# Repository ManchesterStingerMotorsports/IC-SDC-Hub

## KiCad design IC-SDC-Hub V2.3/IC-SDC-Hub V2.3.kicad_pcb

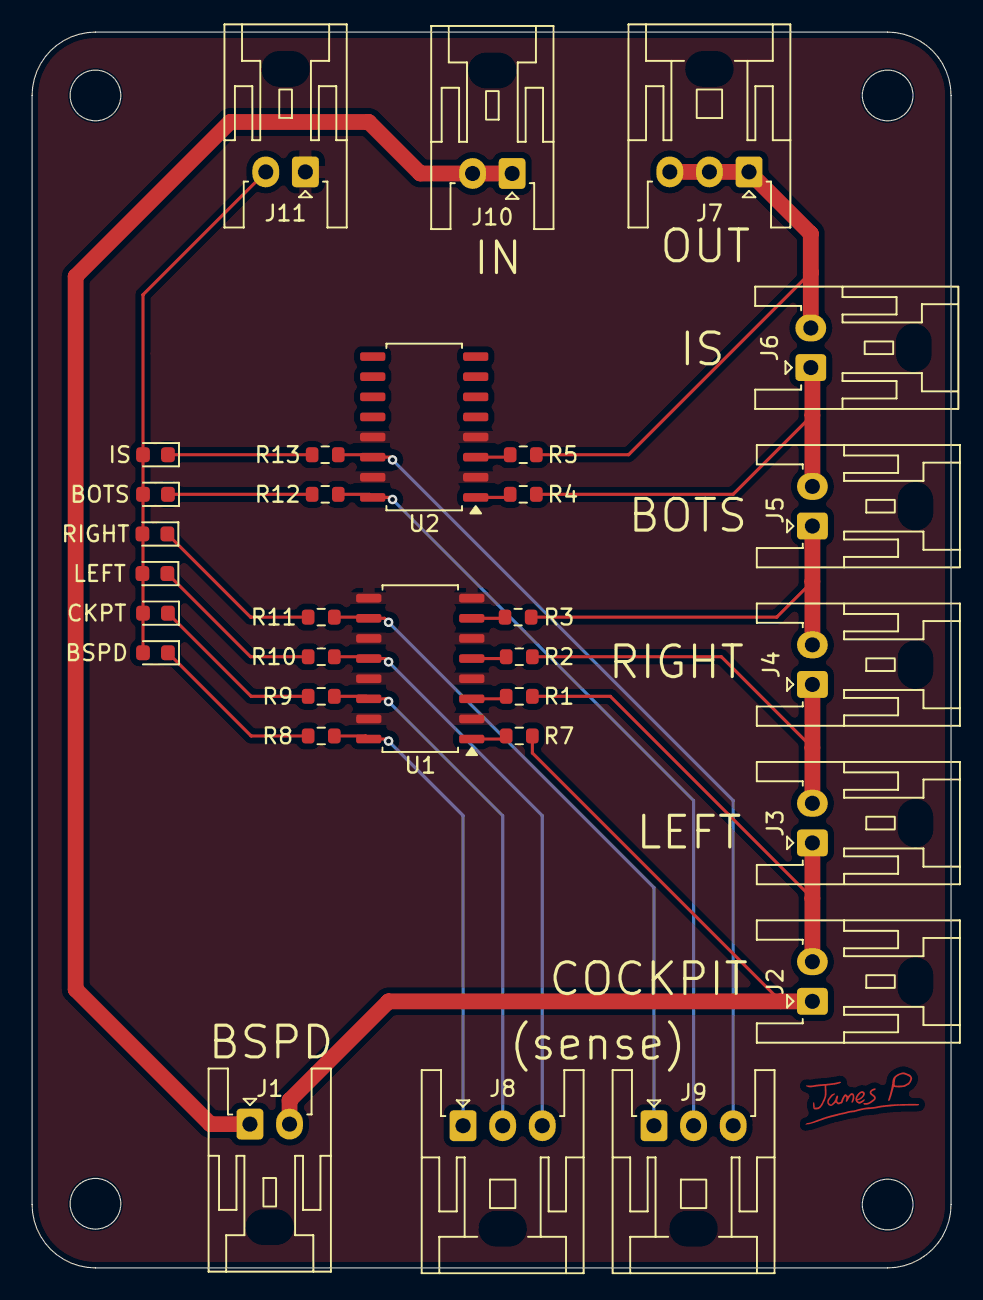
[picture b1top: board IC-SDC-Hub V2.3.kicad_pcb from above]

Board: 2 copper layers, 58.0 x 78.0 mm, 31 parts (0 on the bottom side), 27 nets.

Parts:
BOTS: LED; LED_0603_1608Metric
BSPD: LED; LED_0603_1608Metric
CKPT: LED; LED_0603_1608Metric
IS: LED; LED_0603_1608Metric
J1, J2, J3, J4, J5, J6, J10, J11: JST-XA; JST_XA_S02B-XASK-1_1x02_P2.50mm_Horizontal
J7, J8, J9: Conn_01x03; JST_XA_S03B-XASK-1_1x03_P2.50mm_Horizontal
LEFT: LED; LED_0603_1608Metric
R1, R2, R3, R4, R5, R7: 4k7; R_0603_1608Metric
R8, R9, R10, R11, R12, R13: 2k2; R_0603_1608Metric
RIGHT: LED; LED_0603_1608Metric
U1, U2: TLP293-4; SOIC-16_4.55x10.3mm_P1.27mm

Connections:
+3V3: BOTS.2 (A), BSPD.2 (A), CKPT.2 (A), IS.2 (A), J11.2, LEFT.2 (A), RIGHT.2 (A)
BOTS: J5.2, J6.1, R4.2
BOTS_S: J9.2, R12.2, U2.16
BSPD: J1.2, J2.1, R7.2
BSPD_S: J8.1, R8.2, U1.16
CK_S: J8.2, R9.2, U1.14
COCKPIT: J2.2, J3.1, R1.2
GND: J11.1, U1.2, U1.4, U1.6, U1.8, U1.9, U1.11, U1.13, U1.15, U2.2, U2.4, U2.13, U2.15
INERTIA SWITCH: J6.2, J7.1, J7.2, J7.3, R5.2
IS_S: J9.3, R13.2, U2.14
LEFT: J3.2, J4.1, R2.2
L_S: J8.3, R10.2, U1.12
unnamed: BSPD.1 (K), R8.1
unnamed: CKPT.1 (K), R9.1
unnamed: LEFT.1 (K), R10.1
unnamed: R11.1, RIGHT.1 (K)
unnamed: BOTS.1 (K), R12.1
unnamed: IS.1 (K), R13.1
unnamed: J1.1, J10.1, J10.2
unnamed: R1.1, U1.3
unnamed: R2.1, U1.5
unnamed: R3.1, U1.7
unnamed: R4.1, U2.1
unnamed: R5.1, U2.3
unnamed: R7.1, U1.1
RIGHT: J4.2, J5.1, R3.2
R_S: J9.1, R11.2, U1.10

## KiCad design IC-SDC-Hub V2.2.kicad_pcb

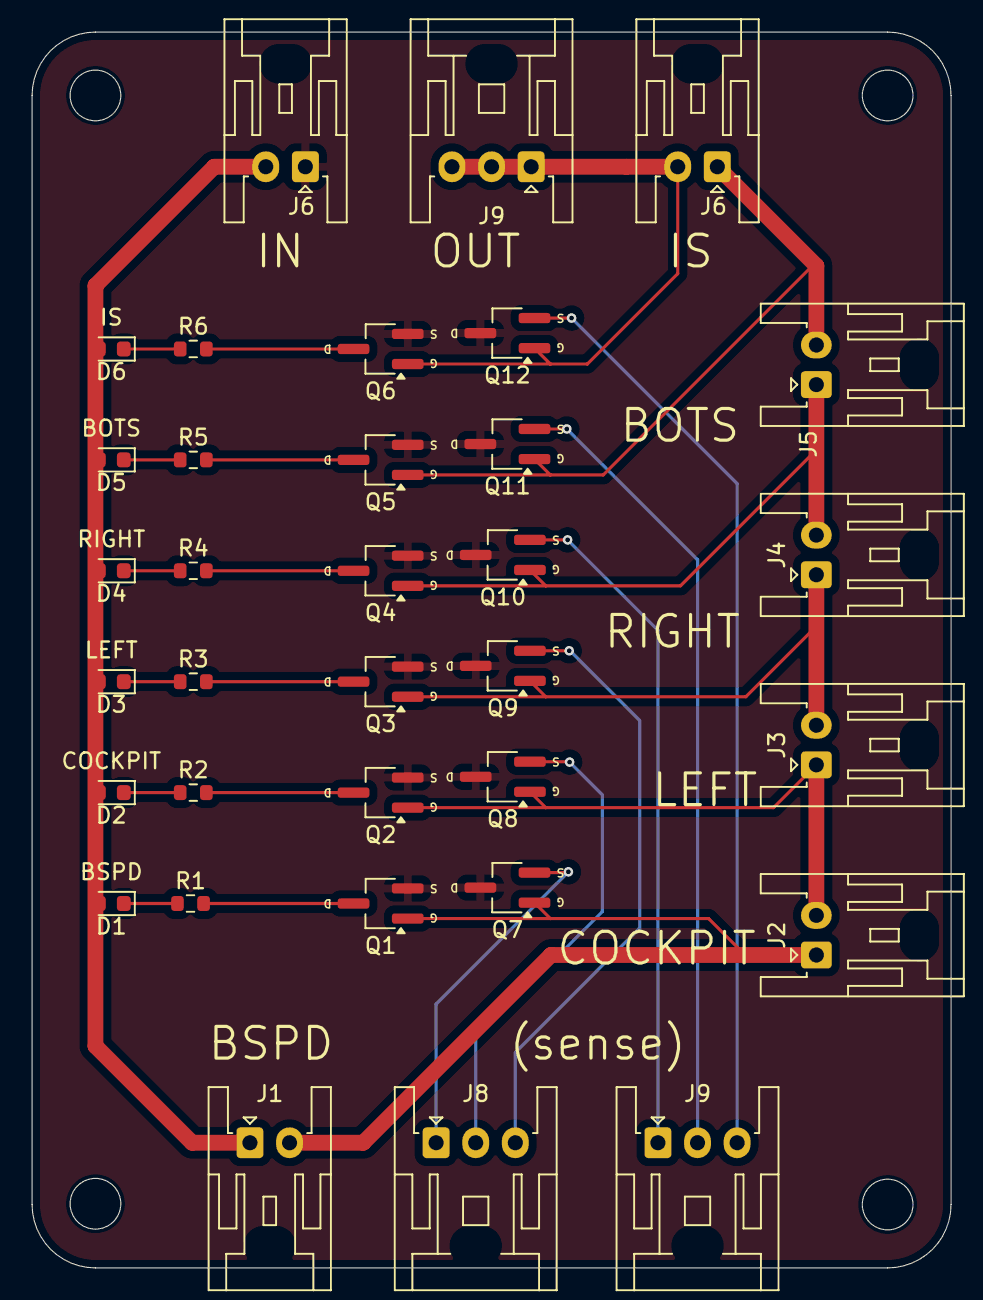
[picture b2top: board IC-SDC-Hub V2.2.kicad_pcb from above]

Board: 2 copper layers, 58.0 x 78.0 mm, 34 parts (0 on the bottom side), 26 nets.

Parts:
D1, D2, D3, D4, D5, D6: LED; LED_0603_1608Metric
J1, J2, J3, J4, J5, J6, J6#2: JST-XA; JST_XA_S02B-XASK-1_1x02_P2.50mm_Horizontal
J8, J9, J9#2: Conn_01x03; JST_XA_S03B-XASK-1_1x03_P2.50mm_Horizontal
Q1, Q2, Q3, Q4, Q5, Q6, Q7, Q8, Q9, Q10, Q11, Q12: BSS205N; MOSFET_Single_SOT-23
R1, R2, R3, R4, R5, R6: 1k; R_0603_1608Metric

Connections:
BOTS_OK: J5.2, J6#2.1, Q5.1 (G), Q11.1 (G)
BOTS_S: J9#2.2, Q11.2 (S)
BSPD_OK: J1.2, J2.1, Q1.1 (G), Q7.1 (G)
BSPD_S: J8.1, Q7.2 (S)
CK_OK: J2.2, J3.1, Q2.1 (G), Q8.1 (G)
CK_S: J8.2, Q8.2 (S)
GND: J6.1, Q1.2 (S), Q2.2 (S), Q3.2 (S), Q4.2 (S), Q5.2 (S), Q6.2 (S), Q7.3 (D), Q8.3 (D), Q9.3 (D), Q10.3 (D), Q11.3 (D), Q12.3 (D)
IS_OK: J6#2.2, J9.1, J9.2, J9.3, Q6.1 (G), Q12.1 (G)
IS_S: J9#2.3, Q12.2 (S)
LVMS: D1.2 (A), D2.2 (A), D3.2 (A), D4.2 (A), D5.2 (A), D6.2 (A), J1.1, J6.2
L_OK: J3.2, J4.1, Q3.1 (G), Q9.1 (G)
L_S: J8.3, Q9.2 (S)
unnamed: D1.1 (K), R1.1
unnamed: D2.1 (K), R2.1
unnamed: D3.1 (K), R3.1
unnamed: D4.1 (K), R4.1
unnamed: D5.1 (K), R5.1
unnamed: D6.1 (K), R6.1
unnamed: Q1.3 (D), R1.2
unnamed: Q2.3 (D), R2.2
unnamed: Q3.3 (D), R3.2
unnamed: Q4.3 (D), R4.2
unnamed: Q5.3 (D), R5.2
unnamed: Q6.3 (D), R6.2
R_OK: J4.2, J5.1, Q4.1 (G), Q10.1 (G)
R_S: J9#2.1, Q10.2 (S)

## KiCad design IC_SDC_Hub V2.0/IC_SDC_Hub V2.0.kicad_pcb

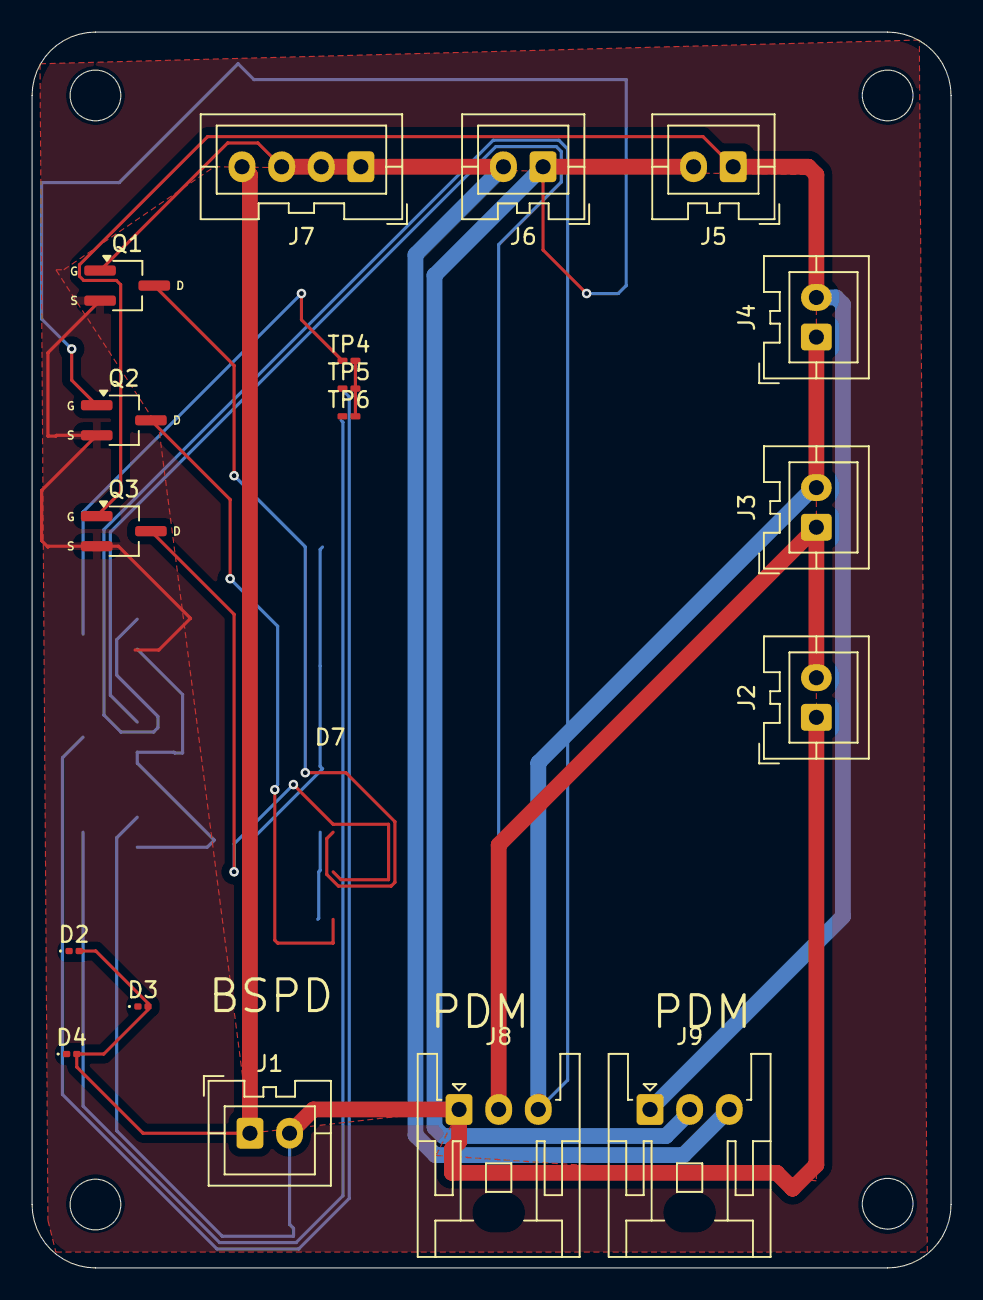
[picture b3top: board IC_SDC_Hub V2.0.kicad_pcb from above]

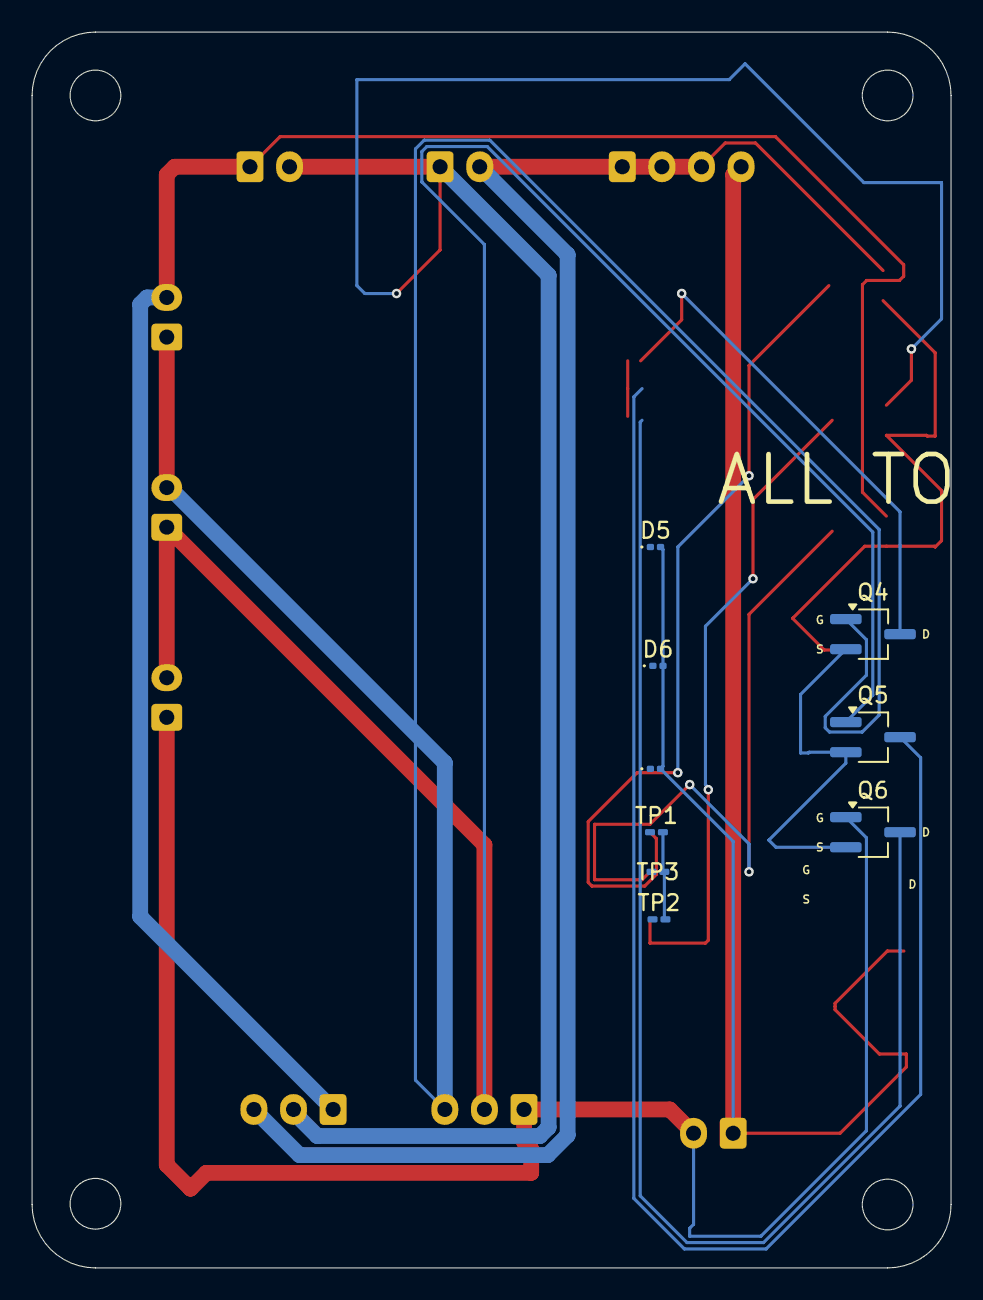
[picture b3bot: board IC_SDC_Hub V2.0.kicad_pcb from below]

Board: 2 copper layers, 58.0 x 78.0 mm, 27 parts (9 on the bottom side), 14 nets.

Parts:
D2, D3, D4, D5, D6, D7: LED; LED_0201_0603Metric
J1, J2, J3, J4, J5, J6: JST-XA; Connector_JST-XA_2POS
J7: JST-XA; Connector_JST-XA_4POS
J8, J9: Conn_01x03; JST_XA_S03B-XASK-1_1x03_P2.50mm_Horizontal
Q1, Q2, Q3, Q4, Q5, Q6: BSS205N; MOSFET_Single_SOT-23
TP1, TP2, TP3, TP4, TP5, TP6: TestPoint; C_0201_0603Metric_Pad0.64x0.40mm_HandSolder

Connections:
BOTS OK: J5.2, J6.1, J9.2, Q2.1 (G)
BSPD_OK: J1.2, J2.1, J8.1, Q6.1 (G)
CKPT_OK: J2.2, J3.1, J8.2, Q5.1 (G)
GND: Q1.2 (S), Q2.2 (S), Q3.2 (S), Q4.2 (S), Q5.2 (S), Q6.2 (S)
IS_OK: J6.2, J7.1, J7.2, J7.3, J9.3, Q1.1 (G)
LEFT_OK: J3.2, J4.1, J8.3, Q4.1 (G)
LVMS: D2.2 (A), D3.2 (A), D4.2 (A), D5.2 (A), D6.2 (A), D7.2 (A), J1.1, J7.4
unnamed: Q1.3 (D), TP1.1
unnamed: Q2.3 (D), TP2.1
unnamed: Q3.3 (D), TP3.1
unnamed: Q4.3 (D), TP4.1
unnamed: Q5.3 (D), TP5.1
unnamed: Q6.3 (D), TP6.1
RIGHT_OK: J4.2, J5.1, J9.1, Q3.1 (G)

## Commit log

2025-11-05 Add base schematic
2025-11-06 Updated to match connector spec
2025-11-06 Updated connectors
2025-11-10 Add .gitignore for KiCad project files
2025-11-18 Add SDC Status Connectors
    to be compatiable with new PDM
2026-02-08 Commit V2.1
    changed connector layout to include separate in/out connectors;
    changed board layout a bit
    removed redundant testpoints
    fixed existing problems with footprints
2026-02-08 Commit V2.1
    change connector layout (separate in/out connectors);
    remove redundant testpoints
    change board layout/component placement a bit
    fix footprint troubles
2026-02-08 Add files via upload
    PCB routing done.
2026-02-08 Final mods
    made small changes to routing
    expanded ground plane
2026-02-10 Final?
    Added Fets so sense lines are either 0V or High impedance (open drain)
2026-02-10 Rename IC-SDC-Hub V2.2.kicad_pro to IC-SDC-Hub V2.2/IC-SDC-Hub V2.2.kicad_pro
2026-05-08 final pcb I think
2026-06-09 Ready to order
